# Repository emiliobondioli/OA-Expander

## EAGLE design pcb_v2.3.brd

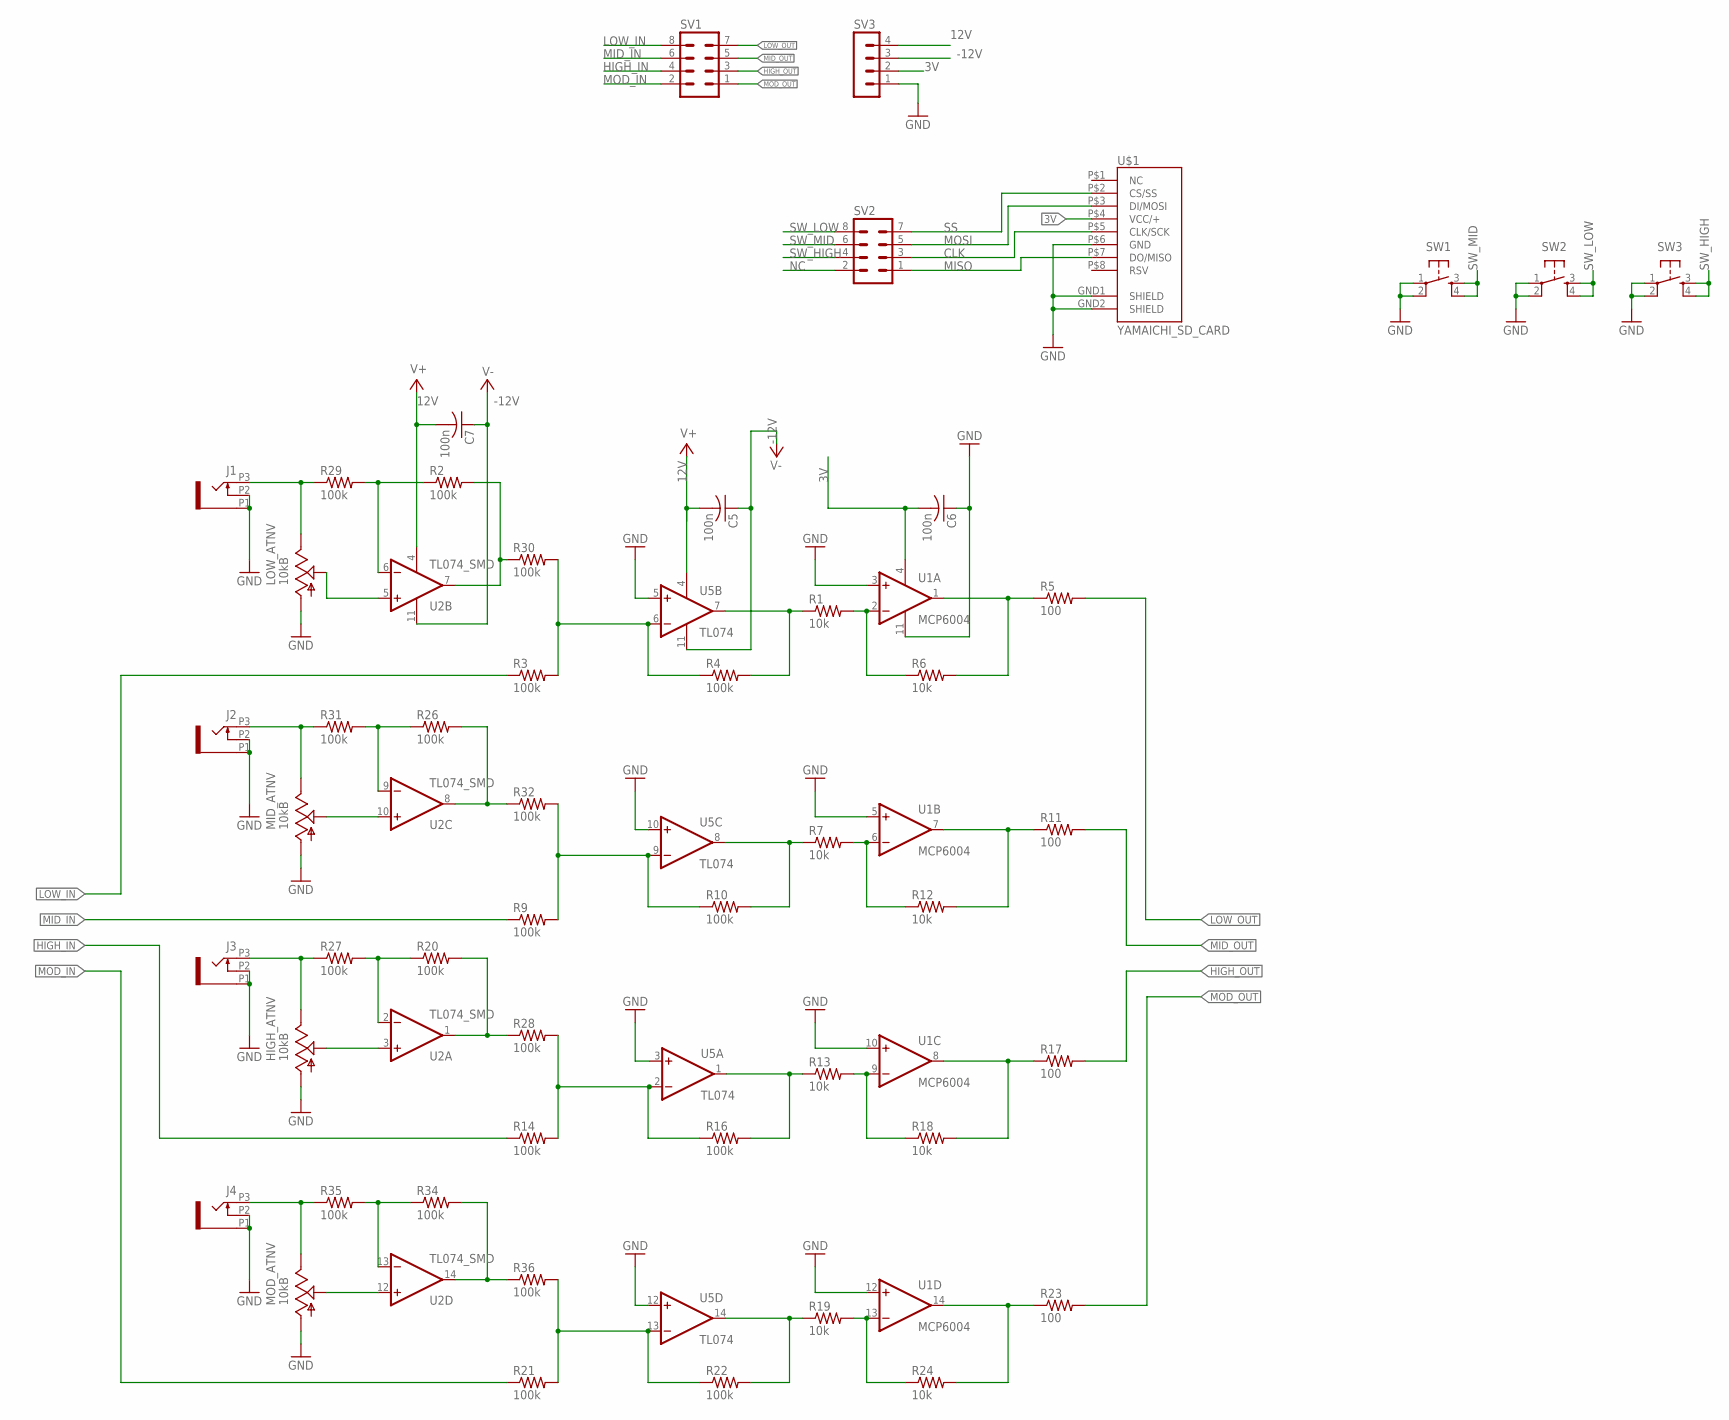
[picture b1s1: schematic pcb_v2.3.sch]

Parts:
C5, C6, C7: 100n; C0603
HIGH_ATNV: 10kB; ALPS_POT_VERTICAL
J1, J2, J3, J4: PJ301_THONKICONN6; WQP_PJ_301M6
LOW_ATNV: 10kB; ALPS_POT_VERTICAL
MID_ATNV: 10kB; ALPS_POT_VERTICAL
MOD_ATNV: 10kB; ALPS_POT_VERTICAL
R1, R6, R7, R12, R13, R18, R19, R24: 10k; R0603
R2, R3, R4, R9, R10, R14, R16, R20, R21, R22, R26, R27, R28, R29, R30, R31, R32, R34, R35, R36: 100k; R0603
R5, R11, R17, R23: 100; R0603
SV1, SV2: MA04-2
SV3: MA04-1
SW1, SW2, SW3: TAC_SWITCHPTH; TACTILE-PTH
U1: MCP6004; SO14
U2: TL074_SMD; SO14
U5: TL074; SO14
U$1: YAMAICHI_SD_CARD; YAMAICHI_MICROSD_VERTICAL

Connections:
3V: C6.2, SV3.2, U1.4 (V+), U$1.P$4 (VCC/+)
12V: C5.2, C7.2, SV3.4, U2.4 (V+), U5.4 (V+)
-12V: C5.1, C7.1, SV3.3, U2.11 (V-), U5.11 (V-)
CLK: SV2.3, U$1.P$5 (CLK/SCK)
GND: C6.1, HIGH_ATNV.P$3 (A), J1.P1 (1), J1.P2 (2), J2.P1 (1), J2.P2 (2), J3.P1 (1), J3.P2 (2), J4.P1 (1), J4.P2 (2), LOW_ATNV.P$3 (A), MID_ATNV.P$3 (A), MOD_ATNV.P$3 (A), SV3.1, SW1.1, SW1.2, SW2.1, SW2.2, SW3.1, SW3.2, U1.3 (+IN), U1.5 (+IN), U1.10 (+IN), U1.11 (V-), U1.12 (+IN), U5.3 (+IN), U5.5 (+IN), U5.10 (+IN), U5.12 (+IN), U$1.GND1 (SHIELD), U$1.GND2 (SHIELD), U$1.P$6 (GND)
HIGH_ATNV_FDBK: R20.1, R27.2, U2.2 (-IN)
HIGH_IN: R14.1, SV1.4
HIGH_OUT: R17.2, SV1.3
HIGH_SUM_OUT: R13.1, R16.2, U5.1 (OUT)
LOW_ATNV_FDBK: R2.1, R29.2, U2.6 (-IN)
LOW_IN: R3.1, SV1.8
LOW_OUT: R5.2, SV1.7
LOW_SUM_OUT: R1.1, R4.2, U5.7 (OUT)
MID_ATNV_FDBK: R26.1, R31.2, U2.9 (-IN)
MID_IN: R9.1, SV1.6
MID_OUT: R11.2, SV1.5
MID_SUM_OUT: R7.1, R10.2, U5.8 (OUT)
MISO: SV2.1, U$1.P$7 (DO/MISO)
MOD_ATNV_FDBK: R34.1, R35.2, U2.13 (-IN)
MOD_IN: R21.1, SV1.2
MOD_OUT: R23.2, SV1.1
MOD_SUM_OUT: R19.1, R22.2, U5.14 (OUT)
MOSI: SV2.5, U$1.P$3 (DI/MOSI)
unnamed: MID_ATNV.P$2 (S), U2.10 (+IN)
unnamed: R1.2, R6.1, U1.2 (-IN)
unnamed: R2.2, R30.1, U2.7 (OUT)
unnamed: LOW_ATNV.P$2 (S), U2.5 (+IN)
unnamed: R5.1, R6.2, U1.1 (OUT)
unnamed: R3.2, R4.1, R30.2, U5.6 (-IN)
unnamed: HIGH_ATNV.P$2 (S), U2.3 (+IN)
unnamed: R9.2, R10.1, R32.2, U5.9 (-IN)
unnamed: R7.2, R12.1, U1.6 (-IN)
unnamed: HIGH_ATNV.P$1 (E), J3.P3 (3), R27.1
unnamed: R20.2, R28.1, U2.1 (OUT)
unnamed: R13.2, R18.1, U1.9 (-IN)
unnamed: R19.2, R24.1, U1.13 (-IN)
unnamed: R11.1, R12.2, U1.7 (OUT)
unnamed: R17.1, R18.2, U1.8 (OUT)
unnamed: R23.1, R24.2, U1.14 (OUT)
unnamed: J1.P3 (3), LOW_ATNV.P$1 (E), R29.1
unnamed: J2.P3 (3), MID_ATNV.P$1 (E), R31.1
unnamed: R26.2, R32.1, U2.8 (OUT)
unnamed: MOD_ATNV.P$2 (S), U2.12 (+IN)
unnamed: J4.P3 (3), MOD_ATNV.P$1 (E), R35.1
unnamed: R34.2, R36.1, U2.14 (OUT)
unnamed: R14.2, R16.1, R28.2, U5.2 (-IN)
unnamed: R21.2, R22.1, R36.2, U5.13 (-IN)
NC: SV2.2
SS: SV2.7, U$1.P$2 (CS/SS)
SW_HIGH: SV2.4, SW3.3, SW3.4
SW_LOW: SV2.8, SW2.3, SW2.4
SW_MID: SV2.6, SW1.3, SW1.4

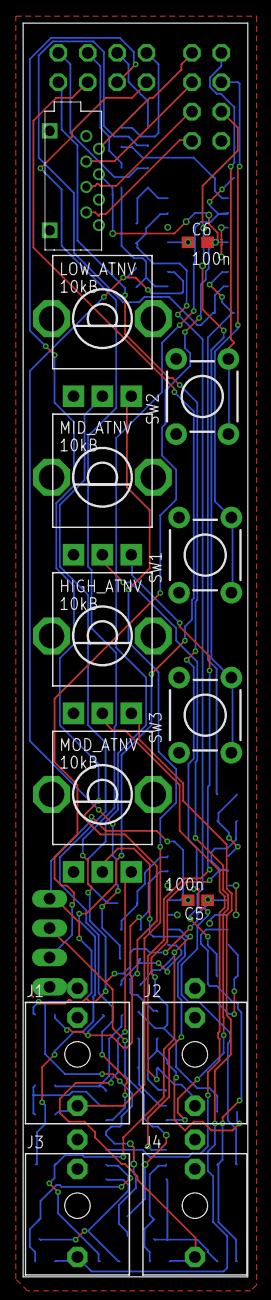
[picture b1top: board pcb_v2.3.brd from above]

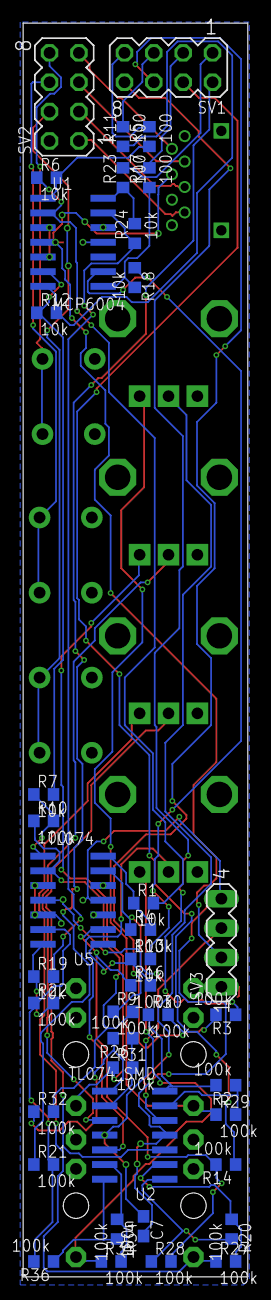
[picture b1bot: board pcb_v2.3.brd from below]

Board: 2 copper layers, 19.4 x 108.4 mm, 53 parts (39 on the bottom side), 51 nets.

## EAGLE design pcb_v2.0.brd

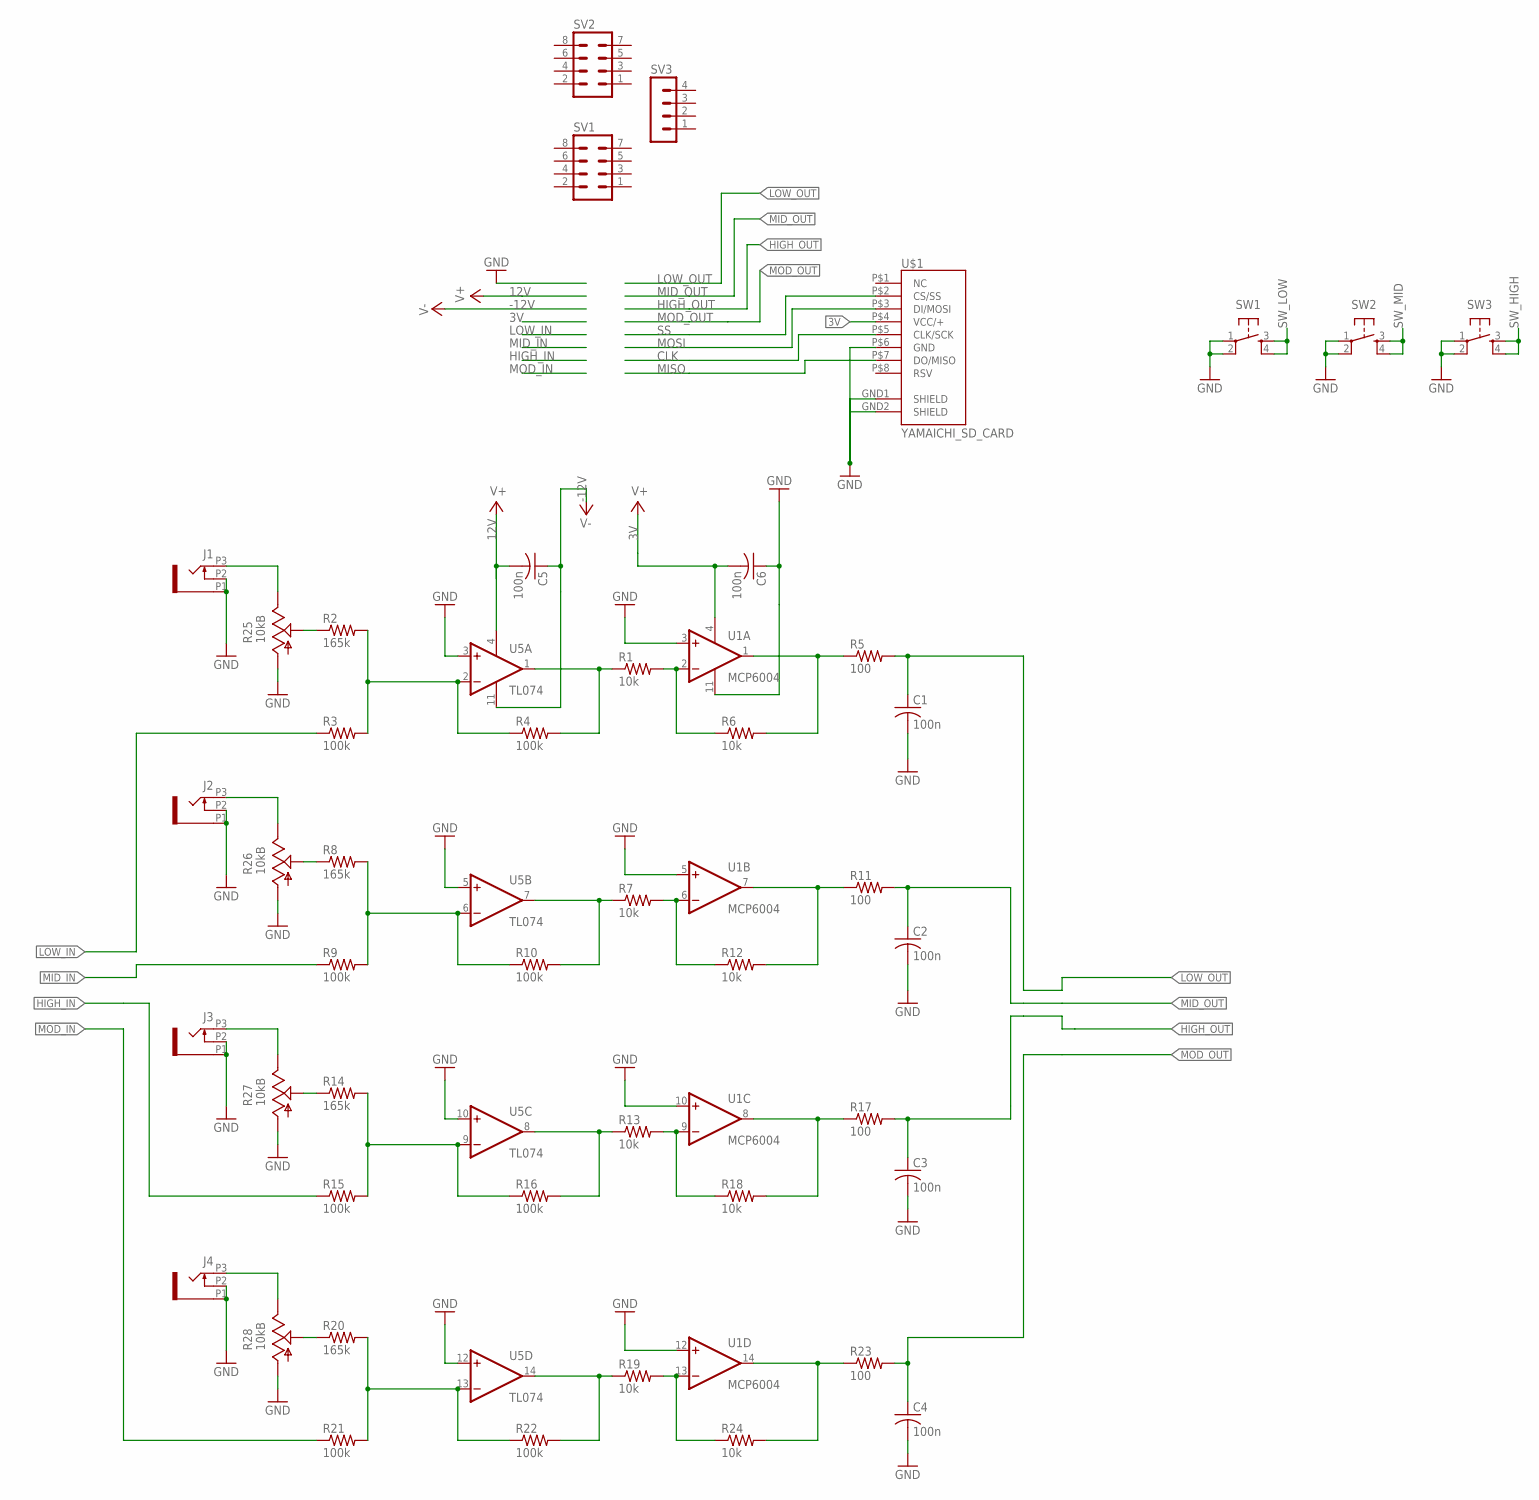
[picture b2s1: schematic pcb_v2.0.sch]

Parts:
C1, C2, C3, C4, C5, C6: 100n; C0603
J1, J2, J3, J4: PJ301_THONKICONN6; WQP_PJ_301M6
R1, R6, R7, R12, R13, R18, R19, R24: 10k; R0603
R2, R8, R14, R20: 165k; R0603
R3, R4, R9, R10, R15, R16, R21, R22: 100k; R0603
R5, R11, R17, R23: 100; R0603
R25, R26, R27, R28: 10kB; ALPS_POT_VERTICAL
SV1, SV2: MA04-2
SV3: MA04-1
SW1, SW2, SW3: TAC_SWITCHPTH; TACTILE-PTH
U1: MCP6004; SO14
U5: TL074; SO14
U$1: YAMAICHI_SD_CARD; YAMAICHI_MICROSD_VERTICAL

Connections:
3V: C6.2, U1.4 (V+)
12V: C5.2, U5.4 (V+)
-12V: C5.1, U5.11 (V-)
CLK: U$1.P$5 (CLK/SCK)
GND: C1.2, C2.2, C3.2, C4.2, C6.1, J1.P1 (1), J1.P2 (2), J2.P1 (1), J2.P2 (2), J3.P1 (1), J3.P2 (2), J4.P1 (1), J4.P2 (2), R25.P$3 (A), R26.P$3 (A), R27.P$3 (A), R28.P$3 (A), SW1.1, SW1.2, SW2.1, SW2.2, SW3.1, SW3.2, U1.3 (+IN), U1.5 (+IN), U1.10 (+IN), U1.11 (V-), U1.12 (+IN), U5.3 (+IN), U5.5 (+IN), U5.10 (+IN), U5.12 (+IN), U$1.GND1 (SHIELD), U$1.GND2 (SHIELD), U$1.P$6 (GND)
HIGH_IN: R15.1
HIGH_OUT: C3.1, R17.2
LOW_IN: R3.1
LOW_OUT: C1.1, R5.2
MID_IN: R9.1
MID_OUT: C2.1, R11.2
MISO: U$1.P$7 (DO/MISO)
MOD_IN: R21.1
MOD_OUT: C4.1, R23.2
MOSI: U$1.P$3 (DI/MOSI)
unnamed: J1.P3 (3), R25.P$1 (E)
unnamed: J2.P3 (3), R26.P$1 (E)
unnamed: R2.2, R3.2, R4.1, U5.2 (-IN)
unnamed: R1.1, R4.2, U5.1 (OUT)
unnamed: R5.1, R6.2, U1.1 (OUT)
unnamed: J3.P3 (3), R27.P$1 (E)
unnamed: J4.P3 (3), R28.P$1 (E)
unnamed: R8.2, R9.2, R10.1, U5.6 (-IN)
unnamed: R7.1, R10.2, U5.7 (OUT)
unnamed: R2.1, R25.P$2 (S)
unnamed: R8.1, R26.P$2 (S)
unnamed: R14.1, R27.P$2 (S)
unnamed: R14.2, R15.2, R16.1, U5.9 (-IN)
unnamed: R13.1, R16.2, U5.8 (OUT)
unnamed: R20.1, R28.P$2 (S)
unnamed: R20.2, R21.2, R22.1, U5.13 (-IN)
unnamed: R19.1, R22.2, U5.14 (OUT)
unnamed: R1.2, R6.1, U1.2 (-IN)
unnamed: R7.2, R12.1, U1.6 (-IN)
unnamed: R13.2, R18.1, U1.9 (-IN)
unnamed: R19.2, R24.1, U1.13 (-IN)
unnamed: R11.1, R12.2, U1.7 (OUT)
unnamed: R17.1, R18.2, U1.8 (OUT)
unnamed: R23.1, R24.2, U1.14 (OUT)
SS: U$1.P$2 (CS/SS)
SW_HIGH: SW3.3, SW3.4
SW_LOW: SW1.3, SW1.4
SW_MID: SW2.3, SW2.4

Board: 2 copper layers, 47 parts (0 on the bottom side), 35 nets, no tracks yet.

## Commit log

2018-07-22 ignore logs
2018-07-22 remove previous versions
2018-07-22 create base schematic for sd card and attenuators
2018-07-23 place v2 components
2018-07-23 new board layout
2018-07-24 route board
2018-07-24 fix switch ordering
2018-07-24 change values layer
